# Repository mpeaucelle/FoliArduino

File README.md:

# FoliArduino
Arduino code, material list and device design for the FoliArduino project

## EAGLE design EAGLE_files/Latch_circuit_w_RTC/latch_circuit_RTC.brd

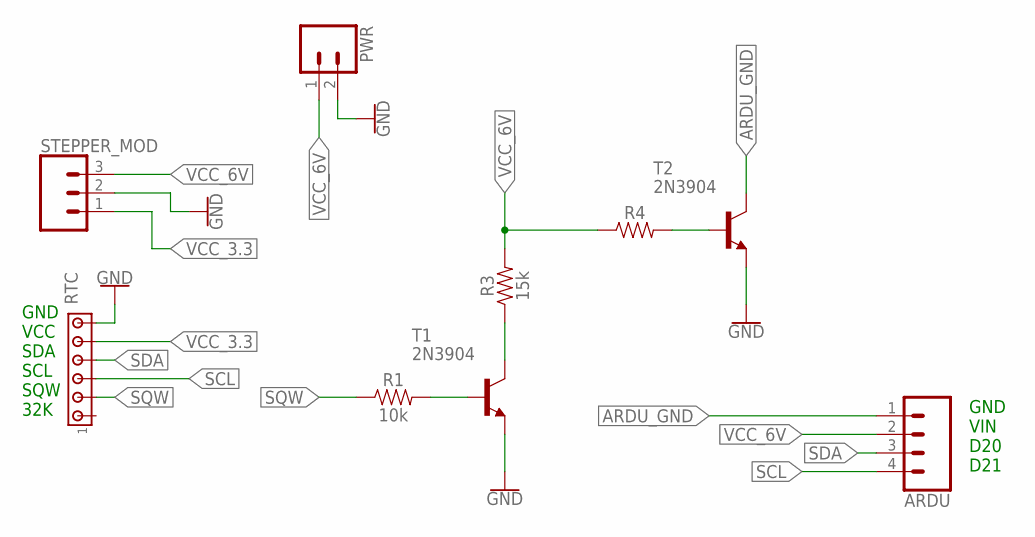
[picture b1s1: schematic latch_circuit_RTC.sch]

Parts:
ARDU: CONN_04PTH; 1X04
PWR: CONN_02; 1X02
R1: 10k; AXIAL-0.3
R3: 15k; AXIAL-0.3
R4: AXIAL-0.3
RTC: MTA06-100; 10X06MTA
STEPPER_MOD: CONN_03; 1X03
T1, T2: 2N3904; TO92

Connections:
ARDU_GND: ARDU.1, T2.1 (C)
GND: PWR.2, RTC.6, STEPPER_MOD.2, T1.3 (E), T2.3 (E)
unnamed: R1.P$2 (2), T1.2 (B)
unnamed: R4.P$2 (2), T2.2 (B)
unnamed: R3.P$1 (1), T1.1 (C)
SCL: ARDU.4, RTC.3
SDA: ARDU.3, RTC.4
SQW: R1.P$1 (1), RTC.2
VCC_3.3: RTC.5, STEPPER_MOD.1
VCC_6V: ARDU.2, PWR.1, R3.P$2 (2), R4.P$1 (1), STEPPER_MOD.3

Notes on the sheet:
GND VCC SDA SCL SQW 32K
GND VIN D20 D21

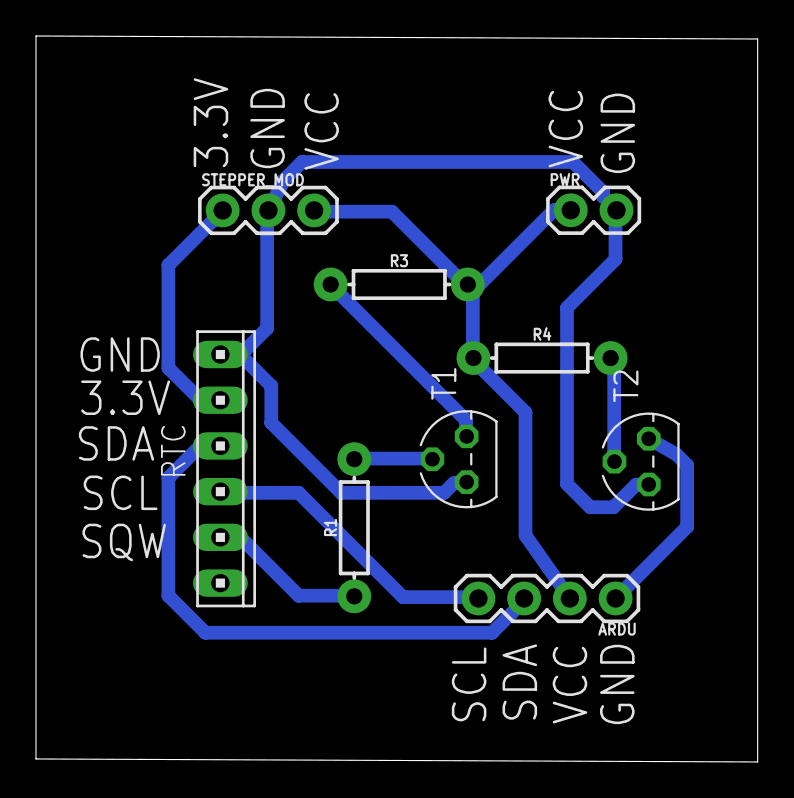
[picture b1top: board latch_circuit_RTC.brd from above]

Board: 2 copper layers, 40.1 x 40.3 mm, 9 parts (0 on the bottom side), 10 nets.

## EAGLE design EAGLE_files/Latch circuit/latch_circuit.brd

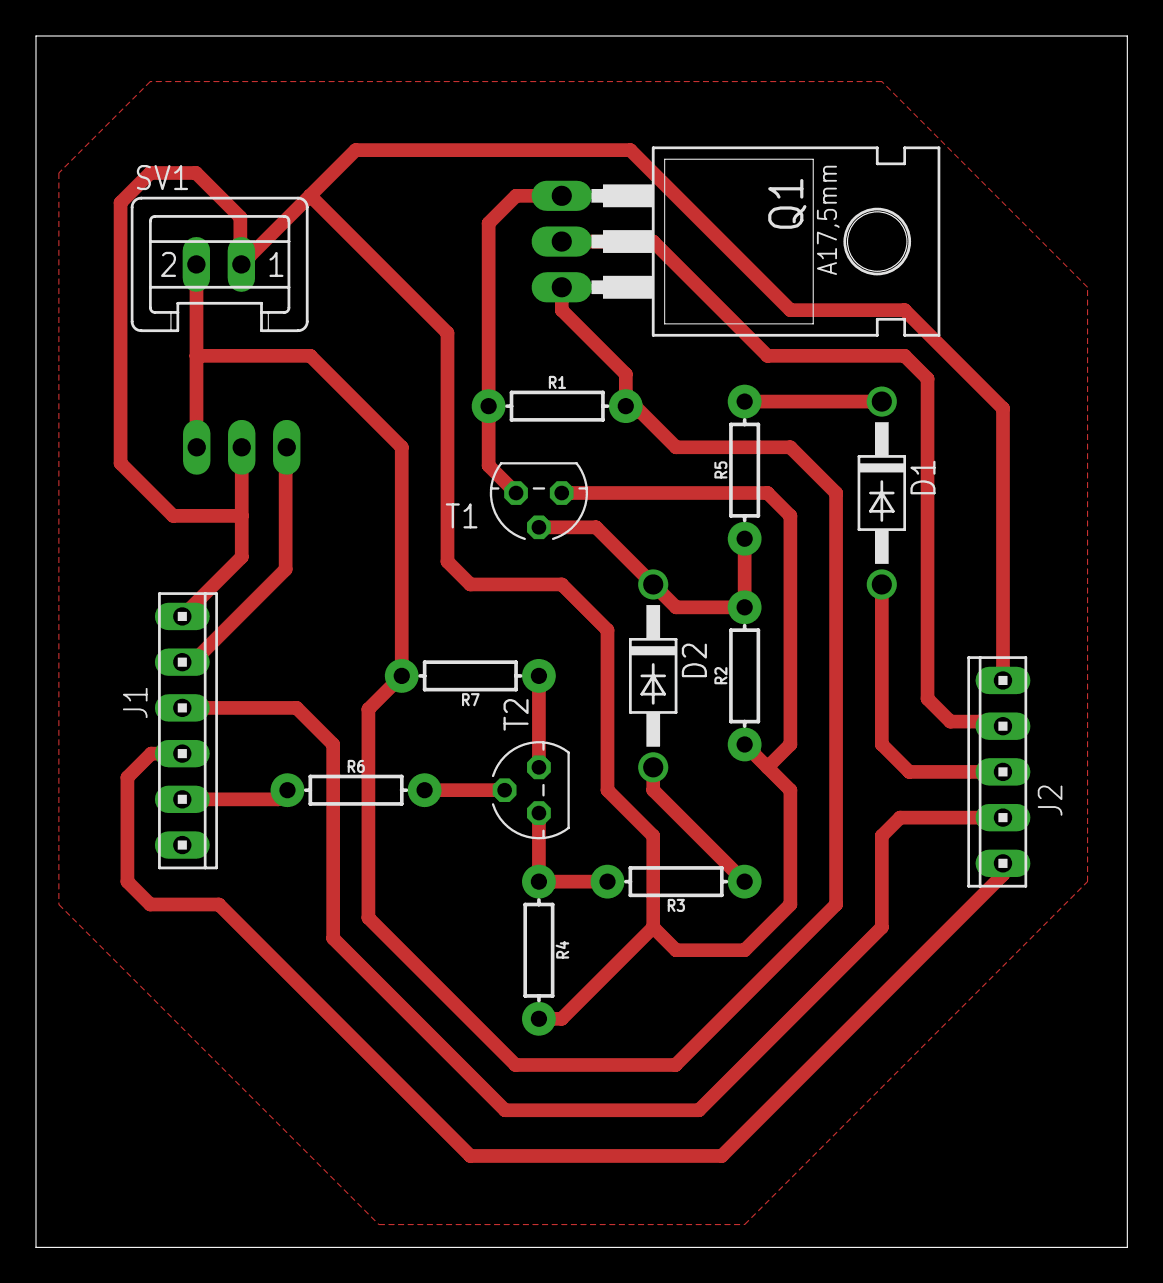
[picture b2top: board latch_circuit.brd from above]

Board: 2 copper layers, 60.6 x 67.3 mm, 16 parts (1 on the bottom side), 15 nets.

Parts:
D1, D2: 1N4933; DO41-10
J1: 10X06MTA
J2: 10X05MTA
Q1: TO220BH
R1, R2: 100k; AXIAL-0.3
R3, R7: 10k; AXIAL-0.3
R4: 220k; AXIAL-0.3
R5: 220; AXIAL-0.3
R6: 1k; AXIAL-0.3
SV1: S02P
SV2: S03P
T1, T2: 2N3904; TO92

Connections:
GND: J1.6, J2.1, R2.P$1, R4.P$2, SV1.1, SV2.2, T1.3
unnamed: Q1.G, R1.P$1, T1.1
unnamed: D2.A, R3.P$1
unnamed: J2.2, Q1.D
unnamed: D2.C, R2.P$2, R5.P$1, T1.2
unnamed: D1.C, R5.P$2
unnamed: D1.A, J2.3
unnamed: J1.2, R6.P$1
unnamed: J1.5, SV2.3
unnamed: J1.4, J2.4
unnamed: J1.3, J2.5
unnamed: R7.P$1, T2.1
unnamed: R6.P$2, T2.2
unnamed: R3.P$2, R4.P$1, T2.3
VCC: Q1.S, R1.P$2, R7.P$2, SV1.2, SV2.1

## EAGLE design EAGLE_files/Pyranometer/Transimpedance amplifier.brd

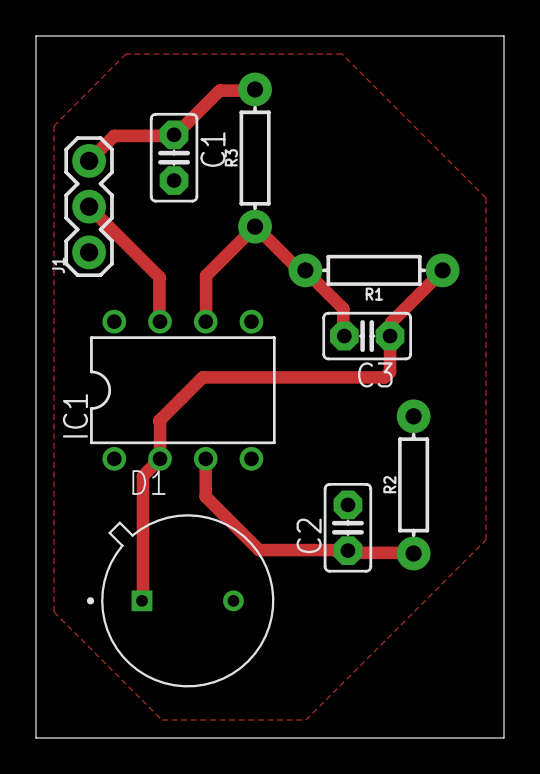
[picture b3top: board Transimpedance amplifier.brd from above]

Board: 2 copper layers, 26.0 x 39.0 mm, 9 parts (0 on the bottom side), 6 nets.

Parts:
C1, C2, C3: C2.5-2
D1: BPW_21; TO254P950H570-2
IC1: LM308N; DIL08
J1: 455-1750-1-ND; 1X03
R1, R2, R3: 1k; AXIAL-0.3

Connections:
GND: C1.2, C2.2, D1.A, IC1.4, J1.1, R2.P$2
unnamed: C3.1, D1.C, IC1.2, R1.P$1
unnamed: C3.2, IC1.6, R1.P$2, R3.P$1
unnamed: C2.1, IC1.3, R2.P$1
unnamed: C1.1, J1.3, R3.P$2
unnamed: IC1.7, J1.2

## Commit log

2020-03-30 Foliarduino v1 timelapse+air+soil
2020-04-06 eagle files
2020-11-11 Measurement of bud temperature with 4 thermocouples
2020-11-12 Changed output format on SD
2020-11-13 Postprocess R script draft
2020-11-13 Added temp to voltage conversion to T-type thermocouple
2020-11-13 Added voltage<->Temp conversion
2020-11-13 Added voltage<->Temp conversion + correction index
2020-11-26 added conversion from µV to mV for hot junction
2020-11-26 Replaced function to read thermocouple voltage
2021-01-14 Corrected Alarm time & Range fault msg
2021-01-14 Added plot function
2021-01-17 Added Latch circuit pdf & png for PCB laser engraving
2021-01-24 Bud temperature data example
2021-01-24 Added Figure
2021-01-24 clean folder
2021-01-25 Added Latch_circuit_RTC eagle files

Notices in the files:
parts and their libraries:
SparkFun-Resistors: Licensing: Creative Commons ShareAlike 4.0 International - https://creativecommons.org/licenses/by-sa/4.0
